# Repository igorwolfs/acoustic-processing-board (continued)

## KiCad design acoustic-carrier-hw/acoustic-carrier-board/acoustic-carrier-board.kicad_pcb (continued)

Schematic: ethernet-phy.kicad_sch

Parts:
C1202, C1205, C1208, C1215, C1224: 10uF; C_0603_1608Metric; MPN CL10A106KP8NNNC
C1203, C1204, C1206, C1207, C1209, C1210, C1216, C1217, C1218, C1219, C1220, C1221, C1222, C1223, C1229: 0.1uF; C_0201_0603Metric; MPN CGA0201X7R104K160ET
C1211, C1212, C1213, C1214, C1225: 10nF; C_0201_0603Metric; MPN 0201B103K250NT
C1226: 100 nF +-5%; C_0603_1608Metric_Pad1.08x0.95mm_HandSolder; MPN CL10B104KB8NNNC
C1227, C1228: 22pF; C_0402_1005Metric; MPN 0402CG220J500NT
D1201: 1N4148WS; D_SOD-323; MPN 1N4148WS
J1201: HR911130A; RJ45-TH_HR911130A; MPN HR911130A
L1201, L1202, L1203: 120@100MHz; L_0603_1608Metric; MPN BLM18SG121TN1D
R1201: 0; R_0402_1005Metric_Pad0.72x0.64mm_HandSolder; MPN 0402WGF0000TCE
R1202: 12k+-1%; R_0603_1608Metric; MPN 0603WAF1202T5E
R1203: 10k; R_0603_1608Metric; MPN 0603WAF1002T5E; not fitted
R1204, R1208, R1212, R1213: 4.7k; R_0402_1005Metric; MPN 0402WGF4701TCE
R1205: 1k; R_0402_1005Metric; MPN 0402WGF1001TCE
R1206, R1209: 470; R_0603_1608Metric; MPN 0603WAF4700T5E
R1207, R1210, R1211: 10k; R_0603_1608Metric; MPN 0603WAF1002T5E
RN1201: 4x4k7; R_Array_Convex_4x0603; MPN 4D03WGJ0472T5E
TP1201: TestPoint; TestPoint_Loop_D1.80mm_Drill1.0mm_Beaded
U1201: KSZ9031RN; QFN-48-1EP_7x7mm_P0.5mm_EP5.15x5.15mm; MPN KSZ9031RNXCC
Y1201: 25MHz; Crystal_SMD_3225-4Pin_3.2x2.5mm; MPN X322525MOB4SI

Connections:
/ETHERNET-PHY/ETH_AC_GND: C1226.1, J1201.1
/ETHERNET-PHY/ETH_GLED_K: J1201.12, R1206.1
/ETHERNET-PHY/ETH_LED_1: R1209.2, R1210.1, U1201.17 (LED1/PHAD0/PME_N1)
/ETHERNET-PHY/ETH_LED_2: R1206.2, R1207.1, U1201.15 (LED2/PHYAD1)
/ETHERNET-PHY/ETH_PHY_A+: J1201.2, U1201.2 (TXRXP_A)
/ETHERNET-PHY/ETH_PHY_A-: J1201.3, U1201.3 (TXRXM_A)
/ETHERNET-PHY/ETH_PHY_B+: J1201.4, U1201.5 (TXRXP_B)
/ETHERNET-PHY/ETH_PHY_B-: J1201.7, U1201.6 (TXRXM_B)
/ETHERNET-PHY/ETH_PHY_C+: J1201.5, U1201.7 (TXRXP_C)
/ETHERNET-PHY/ETH_PHY_C-: J1201.6, U1201.8 (TXRXM_C)
/ETHERNET-PHY/ETH_PHY_D+: J1201.8, U1201.10 (TXRXP_D)
/ETHERNET-PHY/ETH_PHY_D-: J1201.9, U1201.11 (TXRXM_D)
/ETHERNET-PHY/ETH_YLED_K: J1201.13, R1209.1
/ETHERNET-PHY/VDDAH_3V3: C1202.1, C1203.1, C1204.1, L1203.2, U1201.1 (AVDDH), U1201.12 (AVDDH)
/ETHERNET-PHY/VDDAL_1V2: C1208.1, C1209.1, C1210.1, C1211.1, C1212.1, L1201.1, U1201.4 (AVDDL), U1201.9 (AVDDL)
/ETHERNET-PHY/VDDAPLL_1V2: C1205.1, C1206.1, C1207.1, L1202.1, U1201.44 (AVDDL_PLL)
/RGMII_MDIO.CLK: U1201.36 (MDC)
/RGMII_MDIO.DATA: R1205.1, U1201.37 (MDIO)
/RGMII_RX.CLK: R1203.2, R1211.1, U1201.35 (RX_CLK/PHYAD2)
/RGMII_RX.CTL: R1204.1, U1201.33 (RX_DV/CLK125_EN)
/RGMII_RX.D0: RN1201.1 (R1.1), U1201.32 (RXD0/MODE0)
/RGMII_RX.D1: RN1201.2 (R2.1), U1201.31 (RXD1/MODE1)
/RGMII_RX.D2: RN1201.3 (R3.1), U1201.28 (RXD2/MODE2)
/RGMII_RX.D3: RN1201.4 (R4.1), U1201.27 (RXD3/MODE3)
/RGMII_TX.CLK: U1201.24 (GTX_CLK); also elsewhere on the board
/RGMII_TX.CTL: U1201.25 (TX_EN); also elsewhere on the board
/RGMII_TX.D0: U1201.19 (TXD0); also elsewhere on the board
/RGMII_TX.D1: U1201.20 (TXD1); also elsewhere on the board
/RGMII_TX.D2: U1201.21 (TXD2); also elsewhere on the board
/RGMII_TX.D3: U1201.22 (TXD3); also elsewhere on the board
ETH_REFCLK: R1213.1, U1201.41 (CLK125_NDO/LED_MODE); also elsewhere on the board
GND: C1202.2, C1203.2, C1204.2, C1205.2, C1206.2, C1207.2, C1208.2, C1209.2, C1210.2, C1211.2, C1212.2, C1213.2, C1214.2, C1215.2, C1216.2, C1217.2, C1218.2, C1219.2, C1220.2, C1221.2, C1222.2, C1223.2, C1224.2, C1225.2, C1226.2, C1227.1, C1228.1, C1229.2, J1201.10, J1201.S1 (SHIELD), J1201.S2 (SHIELD), R1202.2, R1207.2, R1210.2, R1211.2, R1213.2, U1201.29 (VSS), U1201.49 (PAD_GND), Y1201.2, Y1201.4; also elsewhere on the board
unnamed: C1228.2, R1201.1, Y1201.3
unnamed: R1202.1, U1201.48 (ISET)
unnamed: C1227.2, U1201.46 (XI), Y1201.1
unnamed: R1201.2, U1201.45 (XO)
VCORE_3V3: C1221.1, C1222.1, C1223.1, C1224.1, C1225.1, D1201.1 (K), J1201.11, J1201.14, L1203.1, R1203.1, R1204.2, R1205.2, R1208.2, R1212.2, RN1201.5 (R4.2), RN1201.6 (R3.2), RN1201.7 (R2.2), RN1201.8 (R1.2), U1201.16 (DVDDH), U1201.34 (DVDDH), U1201.40 (DVDDH); also elsewhere on the board
VETH_1V2: C1213.1, C1214.1, C1215.1, C1216.1, C1217.1, C1218.1, C1219.1, C1220.1, L1201.2, L1202.2, U1201.14 (DVDDL), U1201.18 (DVDDL), U1201.23 (DVDDL), U1201.26 (DVDDL), U1201.30 (DVDDL), U1201.39 (DVDDL); also elsewhere on the board
~ETH_INT: R1208.1, U1201.38 (INT_N/PME_N2)
~ETH_RESET: C1229.1, D1201.2 (A), R1212.1, TP1201.1, U1201.42 (RESET_N); also elsewhere on the board

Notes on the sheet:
ETHERNET DECOUPLING
NRESET: - Capacitor discharge on brown-out. - RC-debouncing, tau: r*c = 4.7e3 * 1e-6 = 4.7 ms to reach 63 % - I < 1 mA
CLK125_EN = 1
MDCLK is typically about 1 MHz -2.5 MHz (MAX) MDIO pull-up (1-4.7kOhm) required to DVDDH CLK125_NDO Route into the PLL for possible later use in the DDR-peripheral ETH_PHY_DIFF - Speed here == 1 GHz, so 100 ohm differential impedance is required ETH_TXD, ETH_RXD - Speed here is 125 MHz, T=8ns, so m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
TRI-COLOR DUAL LED
MODE[3:0] = 1111 RGMII /w All Modes
NRESET
P1: is the center tap on the magnetics PHY-side - Connect to signal GND with 0x1 uF in series P10: Bob-smith termination - Connect to chassis GND (page 67, fig 12-1) LED - Vf: 2.4 V, I = 1 mA approx, sourced pin current: 2 mA
ETHERNET_PHY
WOL event on pull-down
DIGITAL
ANALOG

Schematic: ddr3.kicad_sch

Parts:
C1101, C1102, C1103, C1104, C1105, C1106, C1108, C1109, C1110, C1111, C1112, C1118, C1119, C1120, C1121, C1122, C1123, C1124, C1125: 0.1uF; C_0201_0603Metric; MPN CGA0201X7R104K160ET
C1107, C1113: 22uF; C_0603_1608Metric; MPN CL10A226MQ8NRNC
C1114, C1115: 10nF; C_0201_0603Metric; MPN 0201B103K250NT
IC1101: MT41K256M16TW-107_P; BGA96C80P9X16_800X1400X120; MPN MT41K256M16TW-107:P
L1101, L1102: 120@100MHz; L_0603_1608Metric; MPN BLM18SG121TN1D
R1101: 240; R_0603_1608Metric; MPN 0603WAF2400T5E

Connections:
/DDR3/DDR3.A0: IC1101.N3 (A0); also elsewhere on the board
/DDR3/DDR3.A1: IC1101.P7 (A1); also elsewhere on the board
/DDR3/DDR3.A2: IC1101.P3 (A2); also elsewhere on the board
/DDR3/DDR3.A3: IC1101.N2 (A3); also elsewhere on the board
/DDR3/DDR3.A4: IC1101.P8 (A4); also elsewhere on the board
/DDR3/DDR3.A5: IC1101.P2 (A5); also elsewhere on the board
/DDR3/DDR3.A6: IC1101.R8 (A6); also elsewhere on the board
/DDR3/DDR3.A7: IC1101.R2 (A7); also elsewhere on the board
/DDR3/DDR3.A8: IC1101.T8 (A8); also elsewhere on the board
/DDR3/DDR3.A9: IC1101.R3 (A9); also elsewhere on the board
/DDR3/DDR3.A10: IC1101.L7 (A10/AP); also elsewhere on the board
/DDR3/DDR3.A11: IC1101.R7 (A11); also elsewhere on the board
/DDR3/DDR3.A12: IC1101.N7 (A12/BC#); also elsewhere on the board
/DDR3/DDR3.A13: IC1101.T3 (A13); also elsewhere on the board
/DDR3/DDR3.A14: IC1101.T7 (A14); also elsewhere on the board
/DDR3/DDR3.BA0: IC1101.M2 (BA0); also elsewhere on the board
/DDR3/DDR3.BA1: IC1101.N8 (BA1); also elsewhere on the board
/DDR3/DDR3.BA2: IC1101.M3 (BA2); also elsewhere on the board
/DDR3/DDR3.CAS#: IC1101.K3 (CAS#); also elsewhere on the board
/DDR3/DDR3.CK+: IC1101.J7 (CK); also elsewhere on the board
/DDR3/DDR3.CK-: IC1101.K7 (CK#); also elsewhere on the board
/DDR3/DDR3.CKE: IC1101.K9 (CKE); also elsewhere on the board
/DDR3/DDR3.CS#: IC1101.L2 (CS#); also elsewhere on the board
/DDR3/DDR3.DQ0: IC1101.E3 (DQ0); also elsewhere on the board
/DDR3/DDR3.DQ1: IC1101.F7 (DQ1); also elsewhere on the board
/DDR3/DDR3.DQ2: IC1101.F2 (DQ2); also elsewhere on the board
/DDR3/DDR3.DQ3: IC1101.F8 (DQ3); also elsewhere on the board
/DDR3/DDR3.DQ4: IC1101.H3 (DQ4); also elsewhere on the board
/DDR3/DDR3.DQ5: IC1101.H8 (DQ5); also elsewhere on the board
/DDR3/DDR3.DQ6: IC1101.G2 (DQ6); also elsewhere on the board
/DDR3/DDR3.DQ7: IC1101.H7 (DQ7); also elsewhere on the board
/DDR3/DDR3.DQ8: IC1101.D7 (DQ8); also elsewhere on the board
/DDR3/DDR3.DQ9: IC1101.C3 (DQ9); also elsewhere on the board
/DDR3/DDR3.DQ10: IC1101.C8 (DQ10); also elsewhere on the board
/DDR3/DDR3.DQ11: IC1101.C2 (DQ11); also elsewhere on the board
/DDR3/DDR3.DQ12: IC1101.A7 (DQ12); also elsewhere on the board
/DDR3/DDR3.DQ13: IC1101.A2 (DQ13); also elsewhere on the board
/DDR3/DDR3.DQ14: IC1101.B8 (DQ14); also elsewhere on the board
/DDR3/DDR3.DQ15: IC1101.A3 (DQ15); also elsewhere on the board
/DDR3/DDR3.LDM: IC1101.E7 (LDM); also elsewhere on the board
/DDR3/DDR3.LDQS+: IC1101.F3 (LDQS); also elsewhere on the board
/DDR3/DDR3.LDQS-: IC1101.G3 (LDQS#); also elsewhere on the board
/DDR3/DDR3.ODT: IC1101.K1 (ODT); also elsewhere on the board
/DDR3/DDR3.RAS#: IC1101.J3 (RAS#); also elsewhere on the board
/DDR3/DDR3.RESET#: IC1101.T2 (RESET#); also elsewhere on the board
/DDR3/DDR3.UDM: IC1101.D3 (UDM); also elsewhere on the board
/DDR3/DDR3.UDQS+: IC1101.B7 (UDQS#); also elsewhere on the board
/DDR3/DDR3.UDQS-: IC1101.C7 (UDQS); also elsewhere on the board
/DDR3/DDR3.WE#: IC1101.L3 (WE#); also elsewhere on the board
/DDR3/VDDR_CORE: C1101.1, C1103.1, C1104.1, C1105.1, C1106.1, C1107.1, C1118.1, C1119.1, C1120.1, C1124.1, IC1101.B2 (VDD_1), IC1101.D9 (VDD_2), IC1101.G7 (VDD_3), IC1101.K2 (VDD_4), IC1101.K8 (VDD_5), IC1101.N1 (VDD_6), IC1101.N9 (VDD_7), IC1101.R1 (VDD_8), IC1101.R9 (VDD_9), L1101.1
/DDR3/VDDR_DQ: C1102.1, C1108.1, C1109.1, C1110.1, C1111.1, C1112.1, C1113.1, C1123.1, C1125.1, IC1101.A1 (VDDQ_1), IC1101.A8 (VDDQ_2), IC1101.C1 (VDDQ_3), IC1101.C9 (VDDQ_4), IC1101.D2 (VDDQ_5), IC1101.E9 (VDDQ_6), IC1101.F1 (VDDQ_7), IC1101.H2 (VDDQ_8), IC1101.H9 (VDDQ_9), L1102.1
GND: C1101.2, C1102.2, C1103.2, C1104.2, C1105.2, C1106.2, C1107.2, C1108.2, C1109.2, C1110.2, C1111.2, C1112.2, C1113.2, C1114.2, C1115.2, C1118.2, C1119.2, C1120.2, C1121.2, C1122.2, C1123.2, C1124.2, C1125.2, IC1101.A9 (VSS_1), IC1101.B1 (VSSQ_1), IC1101.B3 (VSS_2), IC1101.B9 (VSSQ_2), IC1101.D1 (VSSQ_3), IC1101.D8 (VSSQ_4), IC1101.E1 (VSS_3), IC1101.E2 (VSSQ_5), IC1101.E8 (VSSQ_6), IC1101.F9 (VSSQ_7), IC1101.G1 (VSSQ_8), IC1101.G8 (VSS_4), IC1101.G9 (VSSQ_9), IC1101.J2 (VSS_5), IC1101.J8 (VSS_6), IC1101.M1 (VSS_7), IC1101.M9 (VSS_8), IC1101.P1 (VSS_9), IC1101.P9 (VSS_10), IC1101.T1 (VSS_11), IC1101.T9 (VSS_12), R1101.2; also elsewhere on the board
unnamed: IC1101.L8 (ZQ), R1101.1
VLPDDR3_1V35: L1101.2, L1102.2; also elsewhere on the board
VLPDRR3_V675: C1114.1, C1115.1, C1121.1, C1122.1, IC1101.H1 (VREFDQ), IC1101.M8 (VREFCA)

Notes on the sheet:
RAM DDR3L
Vref: - The DDR-logic requires an external 0.75 Volts (SSTL-15 standard). - External resistive divider required Vcc: The DDRL-ram requires a 1.35 V supply voltage. - LDO / buck converter DQS-pins - Upper / Lower 8-bit synchronization for data Data-pins: - upper 8 and lower 8 bits must belong to sam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
VREFCA, VREFDQ: - reference voltages separated for data and control/command address - Should be held at 0.675 V
DDR3L DECOUPLING
CLK/CLK# Termination: 6.5.2: differential termination (100 ohms) recommended - NOTE: probably internally implemented inside the DDR3L already

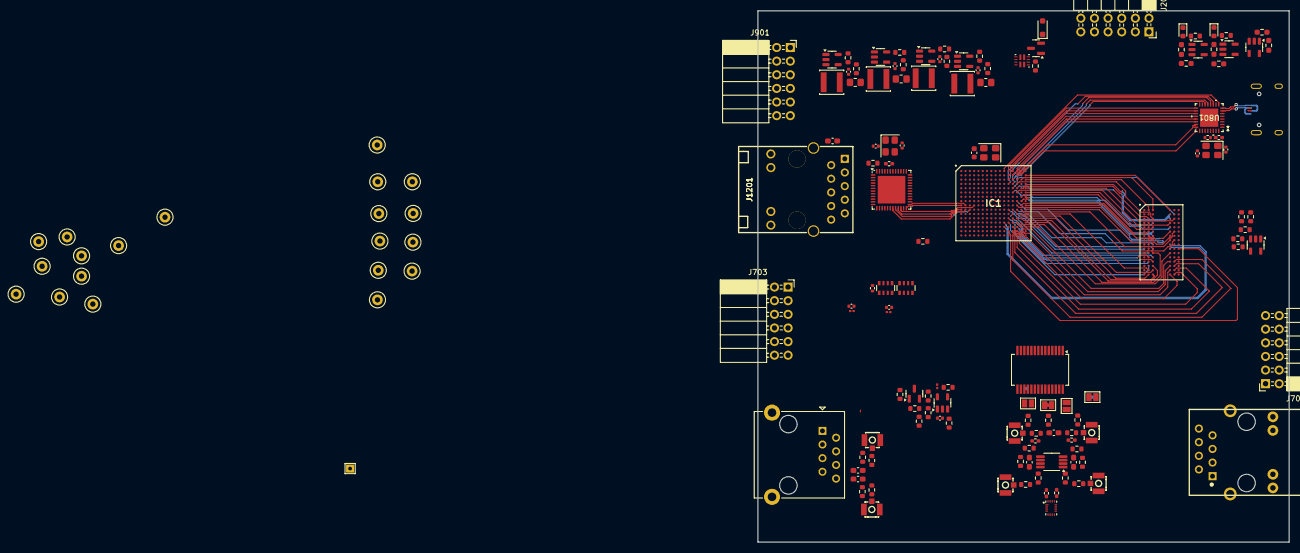
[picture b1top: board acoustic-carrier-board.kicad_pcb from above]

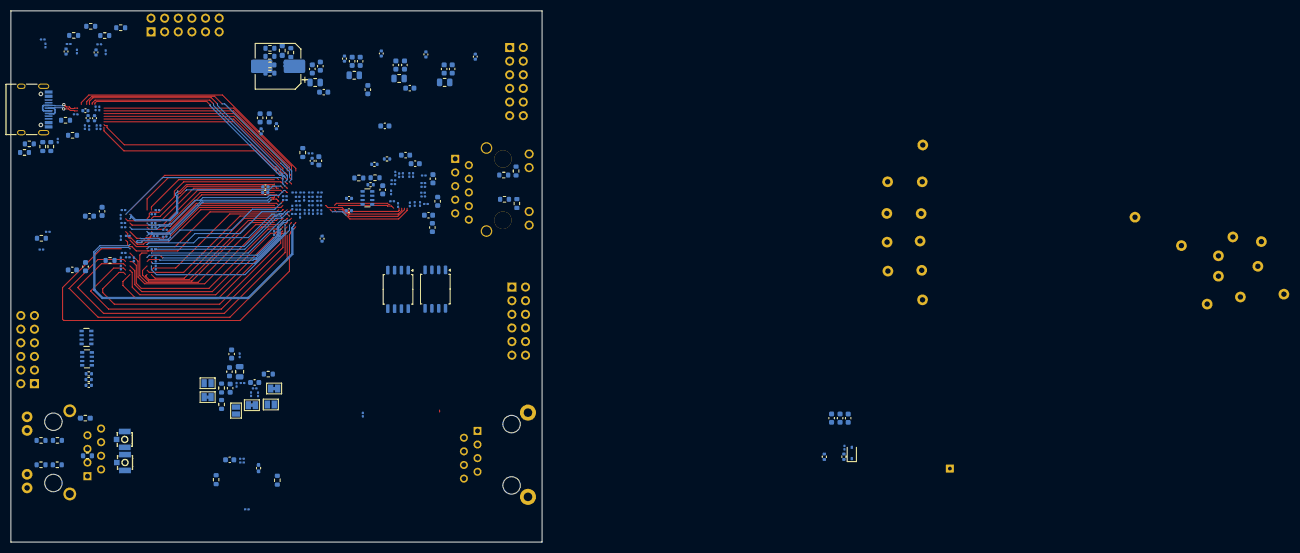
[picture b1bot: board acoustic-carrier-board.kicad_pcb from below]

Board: 6 copper layers, 99.0 x 99.0 mm, 361 parts (212 on the bottom side), 252 nets.

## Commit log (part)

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2025-04-16 added notes
2025-04-18 [resources] Added info on piezo-electrics (PZT)
2025-04-20 [documentation] Added next steps for frequency determination and piezo-selection [next] Go through acousticwaves_chap18, select frequency, check for piezo-element availability and move on to electron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
2025-04-21 [documentation] Added shear and bulk modulus extraction for metals and dielectric [next] Look for further data on 3D printed materials with 100 % filling, check the values extracted
2025-04-22 [theory] Finished theory reading [next] Pick correct piezo-electric based on impedances, shape and resonance frequency
2025-04-22 [todo] Sketched out next steps for testing and circuitn characterization before going into experiments
2025-04-23 [minor] Changed plan - making guestimate of required components first to buy in bulk
2025-04-25 chose driver circuit and fets
2025-04-25 created fet simulation [next] Complete driver circuit for full bridge
2025-04-27 [kicad] Added schematic
2025-04-27 [simulations] Removed tina simulations, added full-bridge simulation with piezo in between [next] Add buck-converter simulation here for fet-driver
2025-04-27 removed todo
2025-04-27 [simulations] Updated sim with new values [kicad] Added inverter circuitry to schematic, add bulk capacitor LCSC parts, add pads for power connections.
2025-04-28 [simulations] Added simulation integrals and parameters
2025-04-29 [kicad] Added analog front-end schematic and MS9280 symbol
2025-04-29 [documentation, kicad] Added decoupling capacitors + input circuitry for adc (next) Look for a decent connector
2025-04-30 [documentation] Researched output power connectors and input connectors (next) select appropriate terminal and rj45 connector
2025-05-01 [kicad] Added connector + input circuit (next) Simulate adc input circuit in ltspice
2025-05-01 added processing info about dsp
2025-05-02 [documentation] Added info on example circuits used, worked on filtering and FPGA info
2025-05-02 [documentation] Found gowin fpga (GW1NR-9) which might fit
2025-05-03 [simulations] Added comments concerning differential vs single-ended filtering
2025-05-03 [documentation] Added info on ECP5 toolchain
2025-05-04 [VHDL] (examples) Went over examples to check global data-flow
2025-05-04 [kicad] Added initial config and jtag circuitrtry, added kicad symbol, added pinout + script for functionality checking (next) add qspi flash for boot
2025-05-04 [kicad] Added flash memory + flash connection (next) Add RAM and ethernet
2025-05-05 [kicad] Chose RAM, connecting pins
2025-05-06 [kicad] re-added passive values after accidental removal
2025-05-06 [simulations] Added 3 buck converter simulations (next) Add fast-switching 13 V buck converter simulation + try improving the switching regulator characteristics with extra 10 uF cap
2025-05-06 [kicad] Added switching regulators for 3.3, 1.25 and 2.5
2025-05-07 [general] Major repo reorganization, separated into carrier-board, power-board, preamp-board
2025-05-07 test
2025-05-08 [carrier] Same as previous [piezodriver] Moved inverter to separate board
2025-05-08 [carrier] Finished buck converters + simulations (next) Connect power to FPGA + add decoupling and bulk capacitance
2025-05-08 added decoupling and power flags
2025-05-09 [carrier] Added decoupling to ethernet PHY
2025-05-10 [carrier] Added usb power + communication circuitry (next) Connect ADC pins to bank 0, select PWM pins, check connectors for power board
2025-05-10 [carrier] Finished basic ADC connections (next) decide on connections with power board
2025-05-11 [piezodriver] Added piezo-driver board connectors
2025-05-11 [piezodriver] Changed piezodriver hardware, (next) create simulations in ltspice, pick components
2025-05-13 [piezodriver] Fixed the basic boost converter simualtion
2025-05-14 [piezodriver] (simulations) figured minimum driving voltage for FET is > 4 V (next) Add Sepic, check behavior > 7.2 V
2025-05-14 [piezodriver] Selection of diode and fet (next) do SEPIC calculations
2025-05-18 [piezodriver] Added notes on sepic calculation
2025-05-18 [piezodriver] Did analysis of SEPIC, went over inherent duty cycle limits, losses, slope compensation, sense resistor and peak current control
2025-05-18 [piezodriver] (ltspice) Added dead-time to full-bridge
2025-05-19 [piezodriver] Added input and output capacitor to 10 V sepic
2025-05-19 [piezodriver] Finished 2 sepic designs, starting boost design (warn) Make sure to max diode voltage difference
2025-05-20 [piezodriver] Finished boost converter simulation and part selection, working on compensation circuit and control loop
2025-05-20 [piezodriver] Finished boost converter dynamics, added compensation circuitry
2025-05-20 [carrier] Reorganized carrier board schematic, added lcsc part numbers (next) check schematic before component placement
2025-05-24 [carrier] Added second adc input with magnetics, added ethernet connector with magnetics [piezodriver] Added diodes to level shifters for gate charge return current
2025-05-24 [piezodriver] Added temperature sensors + ldo + 8x2 connectors to carrier board
2025-05-25 [carrier] removed external led, using ethernet leds, replaced 1kOhm by 470 ohm resistors
2025-05-25 [carrier] Fixed ERC errors and fpga-footprints (next) ) add extra pin functionality to 2 remaining banks, perform schematic checks
2025-05-26 [carrier] added rudimentary LC filter at input (next) - provision signal generator input
2025-05-29 [carrier] Updated requirements for ADC (next) check if you can make the ADC single-ended, add a buffer amplifier
2025-05-29 [carrier] Chose amplifier, changed adc voltage range (next) change commmon mode source, add decoupling, add buffering to common mode
2025-05-31 [carrier] Started tina simulations with th4521
2025-05-31 [carrier] More simulations
2025-06-01 [carrier] Added full simulation with VOCM amplification
2025-06-01 [carrier] Added switch (next) add appropriate test point on secondary dpdt
2025-06-02 [carrier] Replaced voltage reference, added extra 0 ohm resistors, added test-connectors for ADC testing
2025-06-02 [carrier] Fixed ERC issues, added PDn pin connection
2025-06-02 [carrier] Fixed minor symbol errors, added minor routing info (next) continue schematic check
2025-06-02 [carrier] Review of adc_connections-page done
2025-06-03 [carrier] analog frontend check DONE, (next) check config and boot-flash pin connections
2025-06-03 [carrier] Finished flash and config check
2025-06-04 [carrier] Further verification of power board (next) Replace ddr3l reference voltage using TPS51200
2025-06-04 [carrier] Checked power-supply part (next) check ethernet-board
2025-06-04 [carrier] Checked ethernet decoupling + pins + pad + resonator
2025-06-05 [carrier] Added separate buses for ddr3 ctrl-cmd and dq-groups
2025-06-08 [carrier] Doing schmitt trigger calculations and simulations, choosing comparator, choosing USB connector
2025-06-08 [carrier] Finished schmitt trigger for cc1 and cc2 led driver + passive power signalling
2025-06-09 [carrier] Reorganized schematic, moPut adc signals in bus, fixed DRC errors (next) recheck ethernet, check usb, add power switch
2025-06-10 [carrier] Fixed error in ethernet power supply, separated footprints + symbols into library (next) check whether supply should be DVDDH
2025-06-10 [carrier] Added kicad libs and path
2025-06-10 [carrier] Finished switch and reverse voltage circuit
2025-06-11 [carrier] Signal switch-around in ddr3
2025-06-11 [carrier] Added separate schematics for banks
2025-06-11 [carrier] Added hierarchical labels
2025-06-11 [carrier] Added extra decoupling to ECP5U according to datasheet (next) perform page-wise checks, add testpoints
2025-06-12 [¢arrier] Finished checks, startting with layout and routing
2025-06-12 [¢arrier] Checked stackup theory, return current theory (next) continue researching ideal stackup
2025-06-15 [carrier] Added testpoints
2025-06-17 [carrier] Finished rough layout, p (put together according to component category
2025-06-17 [¢arrier] Added netties and determined trace geometry for 50 ohms SE / 100 ohms DIFF impedance (next) reset the appropriate DQS group signals, RGMII and USB signals
2025-06-19 [carrier] Changed non-inverting to inverting schmitt trigger configuration to limit the buffering requirement
2025-06-20 [carrier] connected ethernet, usb and adc to appropriate banks, redpositioned schmitt trigger and USB
2025-06-20 [carrier] Rearanged big parts of the analog PCB
2025-06-21 [carrier] Layout more or less complete (next) think about adding 6x2 connectors, and add extra pin signals to the connector for testing
2025-06-21 [carrier] Added testpoints to rj45, added 6xx2 connectors (next) start routing the digital section
2025-06-21 [carrier] Horizontal DDR3 orientation
2025-06-21 [carrier] Connected the pins to the DDR3 (next) reorient the pins so the first array goes around the DDR3 memory on the first layer, connecting to the back of the BGA
2025-06-22 [carrier] Connected part of DQU
2025-06-22 [carrier] Routing out RGMII interface
2025-06-25 Did big ig parts of routing (next) make sure to re-add pull-ups/downs accordingly
2025-06-26 [carrier] Redid routing to PMOD SPI-flash ah (next) add second PMOD-connector and third connector meant for PWM signalling to power board
2025-06-27 [carrier] Routed 6x2 IO connector
2025-06-27 [carrier] Progressing on ddr3 routing (next) check all ddr3 signals for errors, start length matching
2025-06-28 [carrier] Finished LPDDR3 length-matching (next) finetune clock and spatial lpddr3, finetune rgmii, usb, ..
2025-06-28 [carrier] rerouted USB ULP traces (next) add power planes
2025-06-29 [carrier] Drew power planes at switching converters (next) Drawing power planes at ethernet PHY
2025-06-29 [carrier] Drew all main planes (next) go sheet by sheet connecting decoupling where necessary and drawing reference signals on power plane
2025-07-02 [carrier] Wrote down details on delay calculations
2025-07-02 [carrier] Started writing constraints file for ECP5U-FPGA (next) finish constraints file, try basic synthesis with pins and hello-world
2025-07-03 [¢arrier] Removed logicbone repo, completed config constraints file (next) Build dummy peripherals + test code for RGMII, USB_ULPI, ADC, DDR3
2025-07-05 [carrier] Dummy ddr3 clock peripheral added
2025-07-06 [carrier] Attempting to place and route vhdl verification code (next) move everything to separate VHDL repo
2025-07-06 [carrier] Moved vhdl into separate repo
2025-07-08 [carrier] Added decoupling to LPDDR3 and routed VREF (next) finalize power supply
2025-07-08 [carrier] Further routing, ground plane removal underneath connectors, ..
2025-07-10 [carrier] Added delayed startup + some traces (next) fix the errors inside the DDR3 routing somehow
2025-07-11 [carrier] Corrected most of the DRC errors, a few tens left + respacing DDR3-traces
2025-07-13 [carrier] Fixed most routing errors
2025-07-13 [carrier] Fixed last errors, redid length matching for LPDDR3
2025-07-14 [carrier] Added return vias for LPDDR3, analog, USB and Gb-Eth. Added GND via arrays between power-converters, analog and digital for isolation
2025-07-15 [carrier] Redrew LPDDR3-traces
2025-07-16 [carrier] added silkscreen, moved lpddr3 traces around slightly
2025-07-16 [carrier] finished final review, (next) posting to linkedin, start working on analog front-end board
2025-07-17 [carrier] minor changes and checks
2025-07-17 updated kicad lib
2025-07-22 [carrier] Minor changes in routing documentation
2025-07-23 [carrier] todo: recalculate validity window
2025-07-24 [carrier] Added testpoints to lpddr3 (next) do final checks before ordering
2025-07-26 [carrier] finished for production (next) reroute the LPDDR3, with appropriate CMD-CTRL bus delays, and change banks for command-control
2025-07-28 [carrier] Added testpoints (next) schematic review, (optional) simulation, submit to jlc
2025-07-28 [carrier] Added more return vias (next) move to separate repo
2025-07-28 simplified repo
2025-07-28 added vhdl
2025-07-29 created latest manufacturing files inside production folder
2025-07-31 reorganised folders
2025-08-03 Modified README, lpddr3 testpoint search
2025-08-03 [docs] Cleanup [README] minor modifications
2025-08-07 added step-files
